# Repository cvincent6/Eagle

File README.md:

# Eagle
My Eagle Projects

FlashLED and SoundMeter are examples I did for practice.

RGBBoard is the begining of an LEDCube custom pcb.

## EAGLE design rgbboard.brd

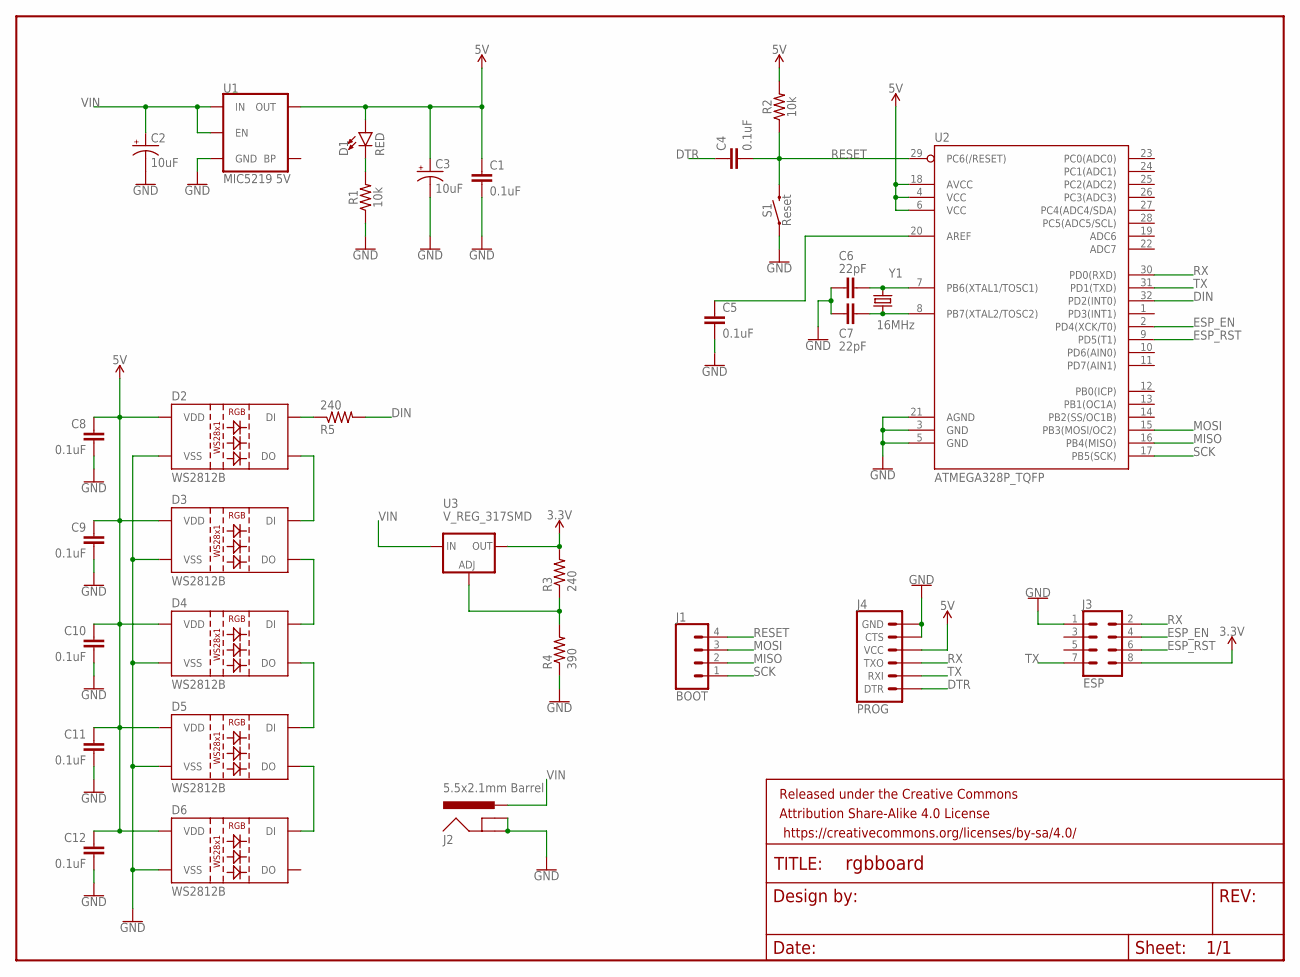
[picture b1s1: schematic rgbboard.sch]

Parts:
C1, C4, C5, C8, C9, C10, C11, C12: 0.1uF; 0603
C2, C3: 10uF; EIA3216
C6, C7: 22pF; 0603
D1: RED; LED-0603
D2, D3, D4, D5, D6: WS2812B
FRAME1: FRAME-LETTER; CREATIVE_COMMONS
J1: BOOT; 1X04
J2: 5.5x2.1mm Barrel; POWER_JACK_SMD
J3: ESP; 2X4
J4: PROG; 1X06
R1, R2: 10k; 0603
R3, R5: 240; R0603
R4: 390; R0603
S1: Reset; TACTILE_SWITCH_SMD_5.2MM
U1: MIC5219 5V; SOT23-5
U2: ATMEGA328P_TQFP; TQFP32-08
U3: V_REG_317SMD; SOT223
Y1: 16MHz; CRYSTAL-SMD-5X3.2-4PAD

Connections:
3.3V: J3.8, R3.2, U3.2 (OUT)
5V: C1.1, C3.+, C8.1, C9.1, C10.1, C11.1, C12.1, D1.A, D2.1 (VDD), D3.1 (VDD), D4.1 (VDD), D5.1 (VDD), D6.1 (VDD), J4.4 (VCC), R2.2, U1.5 (OUT), U2.4 (VCC), U2.6 (VCC), U2.18 (AVCC)
DIN: R5.2, U2.32 (PD2(INT0))
DTR: C4.1, J4.1 (DTR)
ESP_EN: J3.4, U2.2 (PD4(XCK/T0))
ESP_RST: J3.6, U2.9 (PD5(T1))
GND: C1.2, C2.-, C3.-, C5.2, C6.1, C7.1, C8.2, C9.2, C10.2, C11.2, C12.2, D2.3 (VSS), D3.3 (VSS), D4.3 (VSS), D5.3 (VSS), D6.3 (VSS), J2.GND (GNDBREAK), J2.P$4 (GND), J3.1, J4.5 (CTS), J4.6 (GND), R1.1, R4.1, S1.1, S1.2 (1), U1.2 (GND), U2.3 (GND), U2.5 (GND), U2.21 (AGND)
MISO: J1.2, U2.16 (PB4(MISO))
MOSI: J1.3, U2.15 (PB3(MOSI/OC2))
unnamed: D2.2 (DO), D3.4 (DI)
unnamed: D1.C, R1.2
unnamed: D3.2 (DO), D4.4 (DI)
unnamed: D4.2 (DO), D5.4 (DI)
unnamed: D5.2 (DO), D6.4 (DI)
unnamed: C5.1, U2.20 (AREF)
unnamed: C6.2, U2.7 (PB6(XTAL1/TOSC1)), Y1.3 (2)
unnamed: C7.2, U2.8 (PB7(XTAL2/TOSC2)), Y1.1
unnamed: R3.1, R4.2, U3.1 (ADJ)
unnamed: D2.4 (DI), R5.1
RESET: C4.2, J1.4, R2.1, S1.3 (2), S1.4 (2), U2.29 (PC6(/RESET))
RX: J3.2, J4.3 (TXO), U2.30 (PD0(RXD))
SCK: J1.1, U2.17 (PB5(SCK))
TX: J3.7, J4.2 (RXI), U2.31 (PD1(TXD))
VIN: C2.+, J2.VIN0 (PWR), U1.1 (IN), U1.3 (EN), U3.3 (IN)

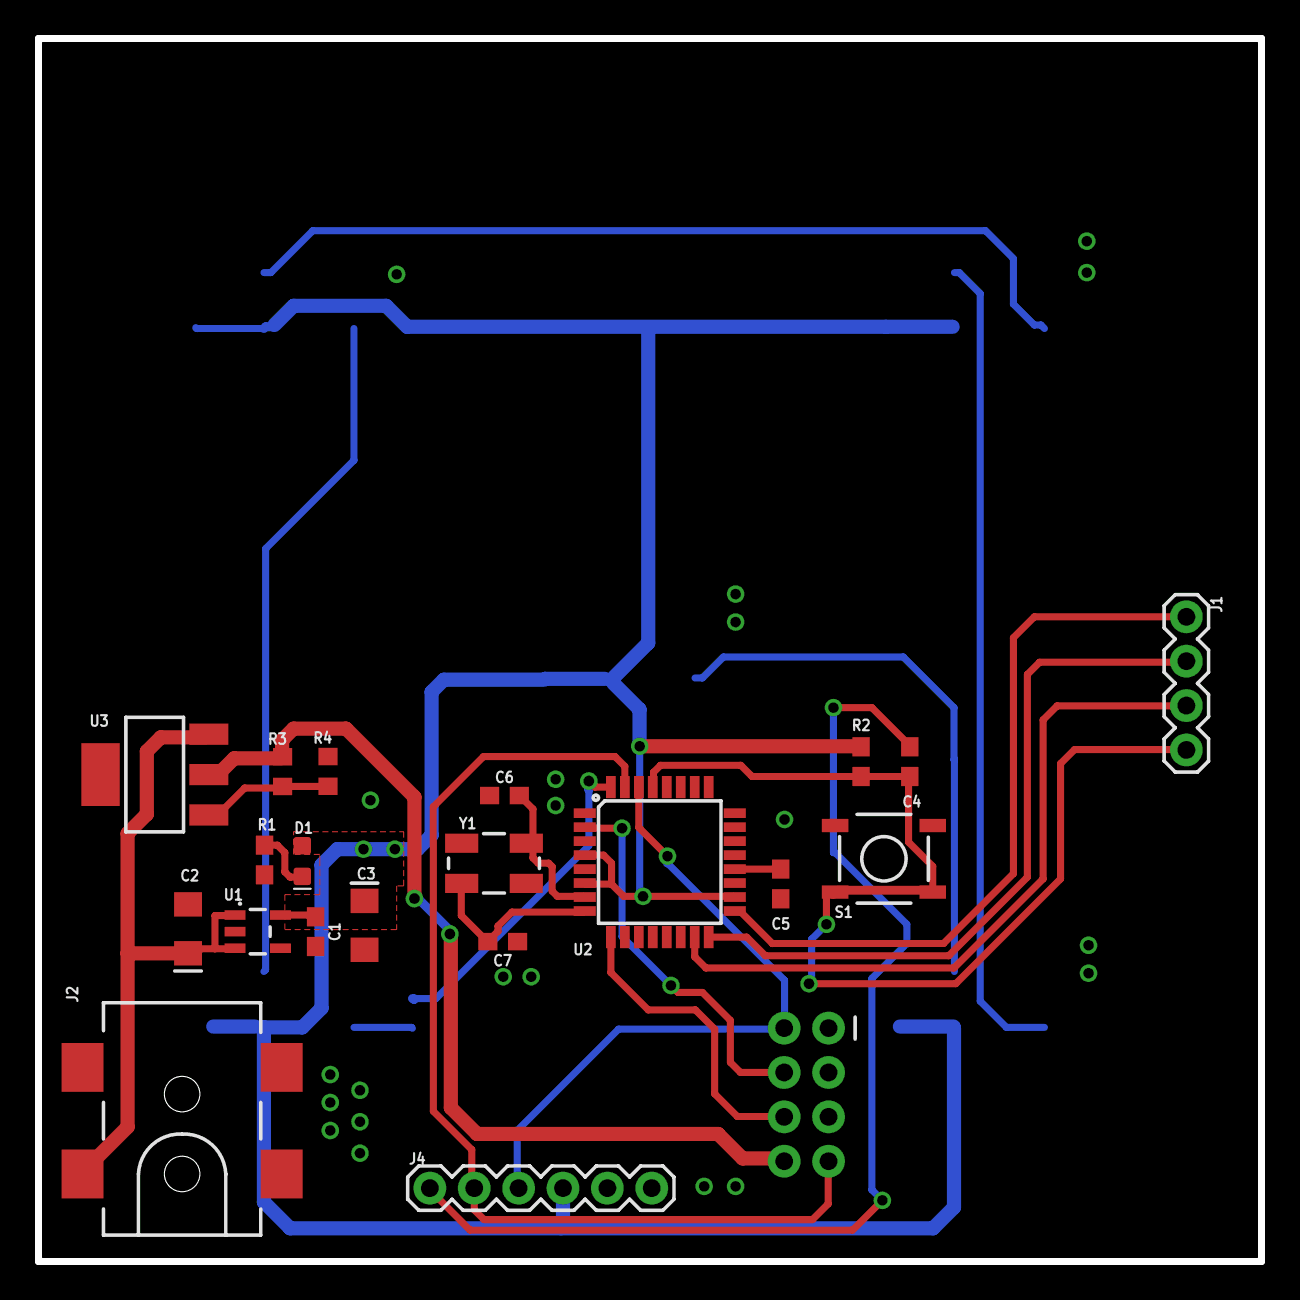
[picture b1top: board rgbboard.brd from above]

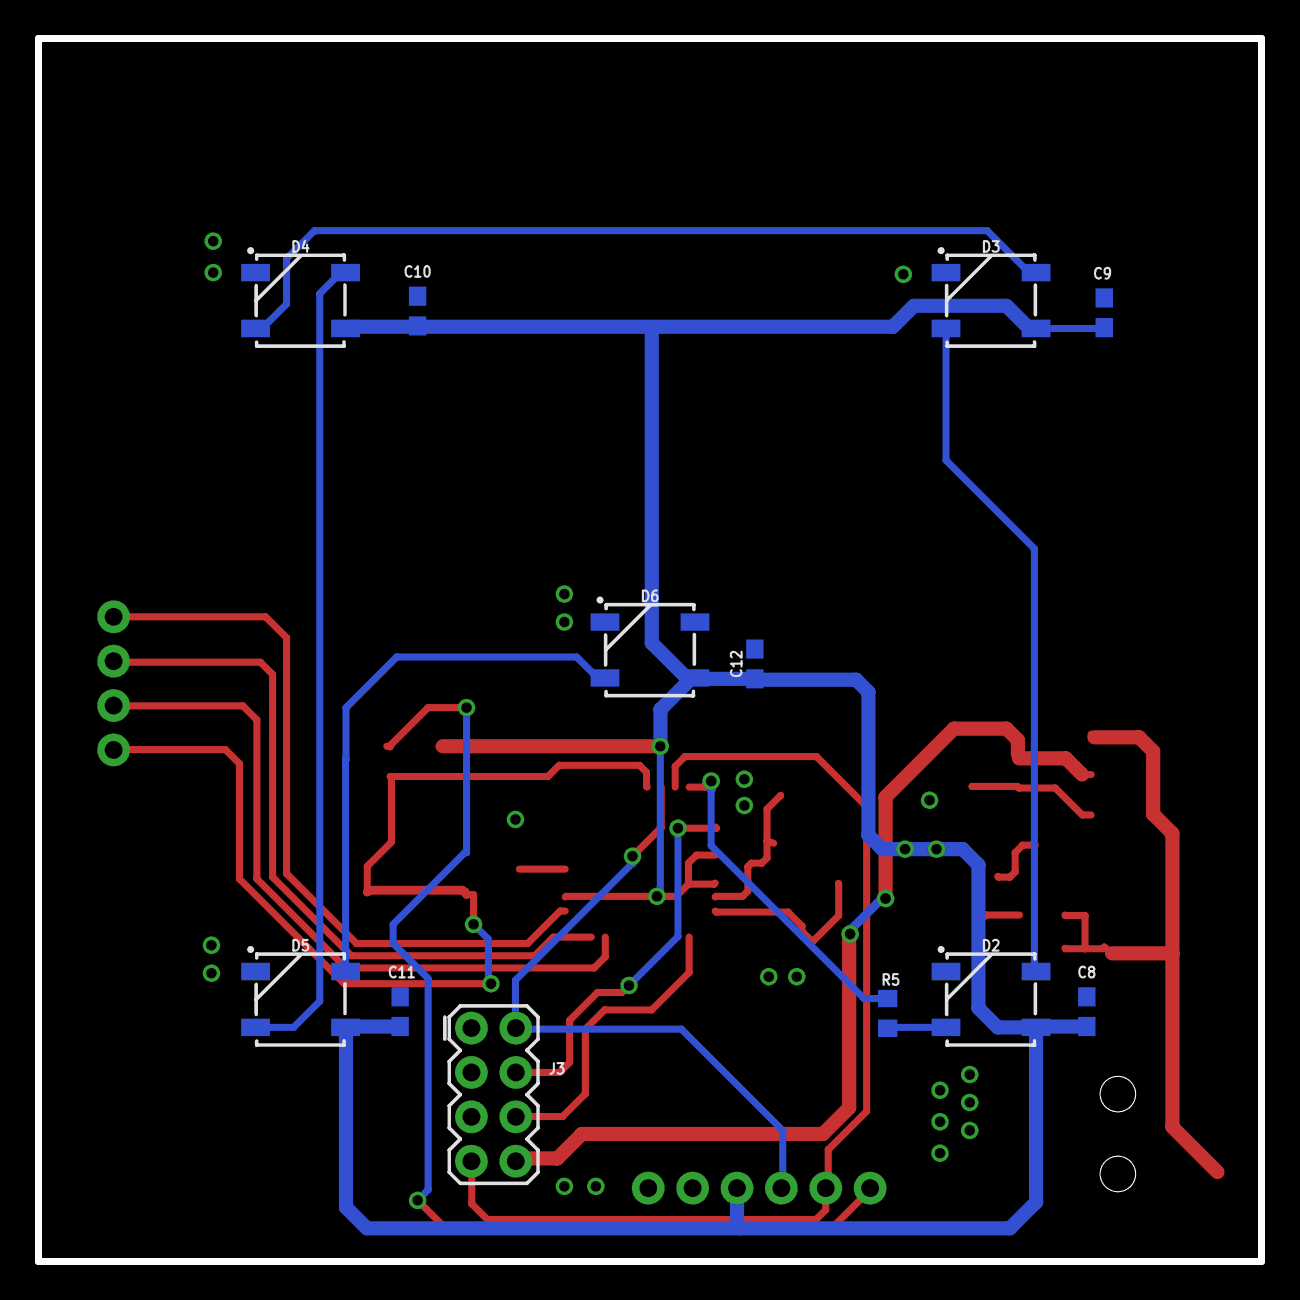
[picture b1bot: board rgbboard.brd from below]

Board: 2 copper layers, 70.0 x 70.0 mm, 33 parts (12 on the bottom side), 24 nets.

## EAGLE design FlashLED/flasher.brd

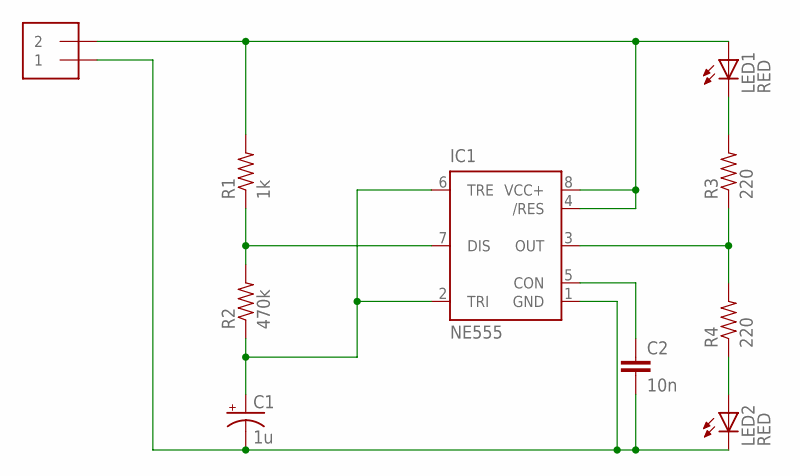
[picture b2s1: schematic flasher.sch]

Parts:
C1: 1u; CPOL-RADIAL-10UF-25V
C2: 10n; CAP-PTH-SMALL
IC1: NE555; DIL-08
J1: 1X2-3.5MM
LED1, LED2: RED; LED5MM
R1: 1k; AXIAL-0.3
R2: 470k; AXIAL-0.3
R3, R4: 220; AXIAL-0.3

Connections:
GND: C1.2 (-), C2.2, IC1.1 (GND), J1.1, LED2.K (C)
unnamed: IC1.7 (DIS), R1.P$1 (1), R2.P$2 (2)
unnamed: C1.1 (+), IC1.2 (TRI), IC1.6 (TRE), R2.P$1 (1)
unnamed: LED2.A, R4.P$1 (1)
unnamed: IC1.3 (OUT), R3.P$1 (1), R4.P$2 (2)
unnamed: LED1.K (C), R3.P$2 (2)
unnamed: C2.1, IC1.5 (CON)
VCC+: IC1.4 (/RES), IC1.8 (VCC+), J1.2, LED1.A, R1.P$2 (2)

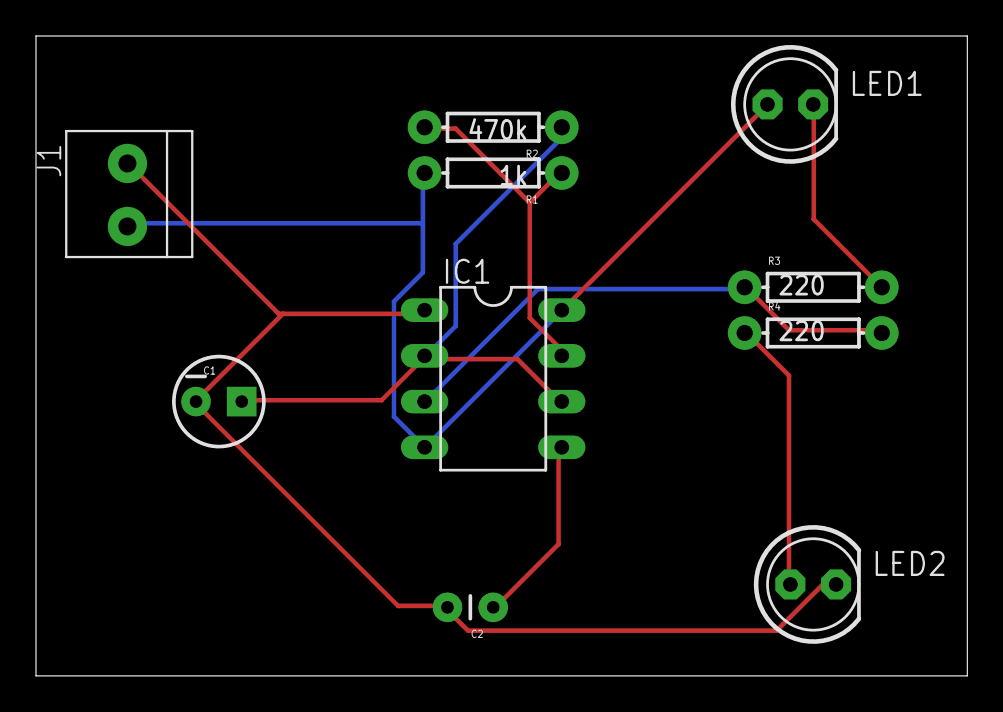
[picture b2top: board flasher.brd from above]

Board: 2 copper layers, 51.7 x 35.5 mm, 10 parts (0 on the bottom side), 8 nets.

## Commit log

2016-10-16 Existing
    Book examples, LED Board personal project
2017-04-05 rgbboard schematic finished
2017-04-05 Layout Done - Need to Pass DRC
2017-04-06 Passes DRC

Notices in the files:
parts and their libraries:
SparkFun-Capacitors: Licensing: Creative Commons ShareAlike 4.0 International - https://creativecommons.org/licenses/by-sa/4.0
SparkFun-Aesthetics: Released under the Creative Commons Attribution Share-Alike 4.0 License
SparkFun-Aesthetics: https://creativecommons.org/licenses/by-sa/4.0
